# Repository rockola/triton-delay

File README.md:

# triton-delay

Triton Delay v2-3 March 2020 by culturejam/@function_fx

These files v2-3_2 2020-03-27 by rockola

## License

"Triton Delay" by culturejam is licensed under [CC BY-SA 4.0](https://creativecommons.org/licenses/by-sa/4.0/).

## More information

[Triton Delay - Adding the "Glide" from EchoCzar to PT2399](https://www.freestompboxes.org/viewtopic.php?f=13&t=30501) on [freestompboxes.org](https://www.freestompboxes.org/)

## Images

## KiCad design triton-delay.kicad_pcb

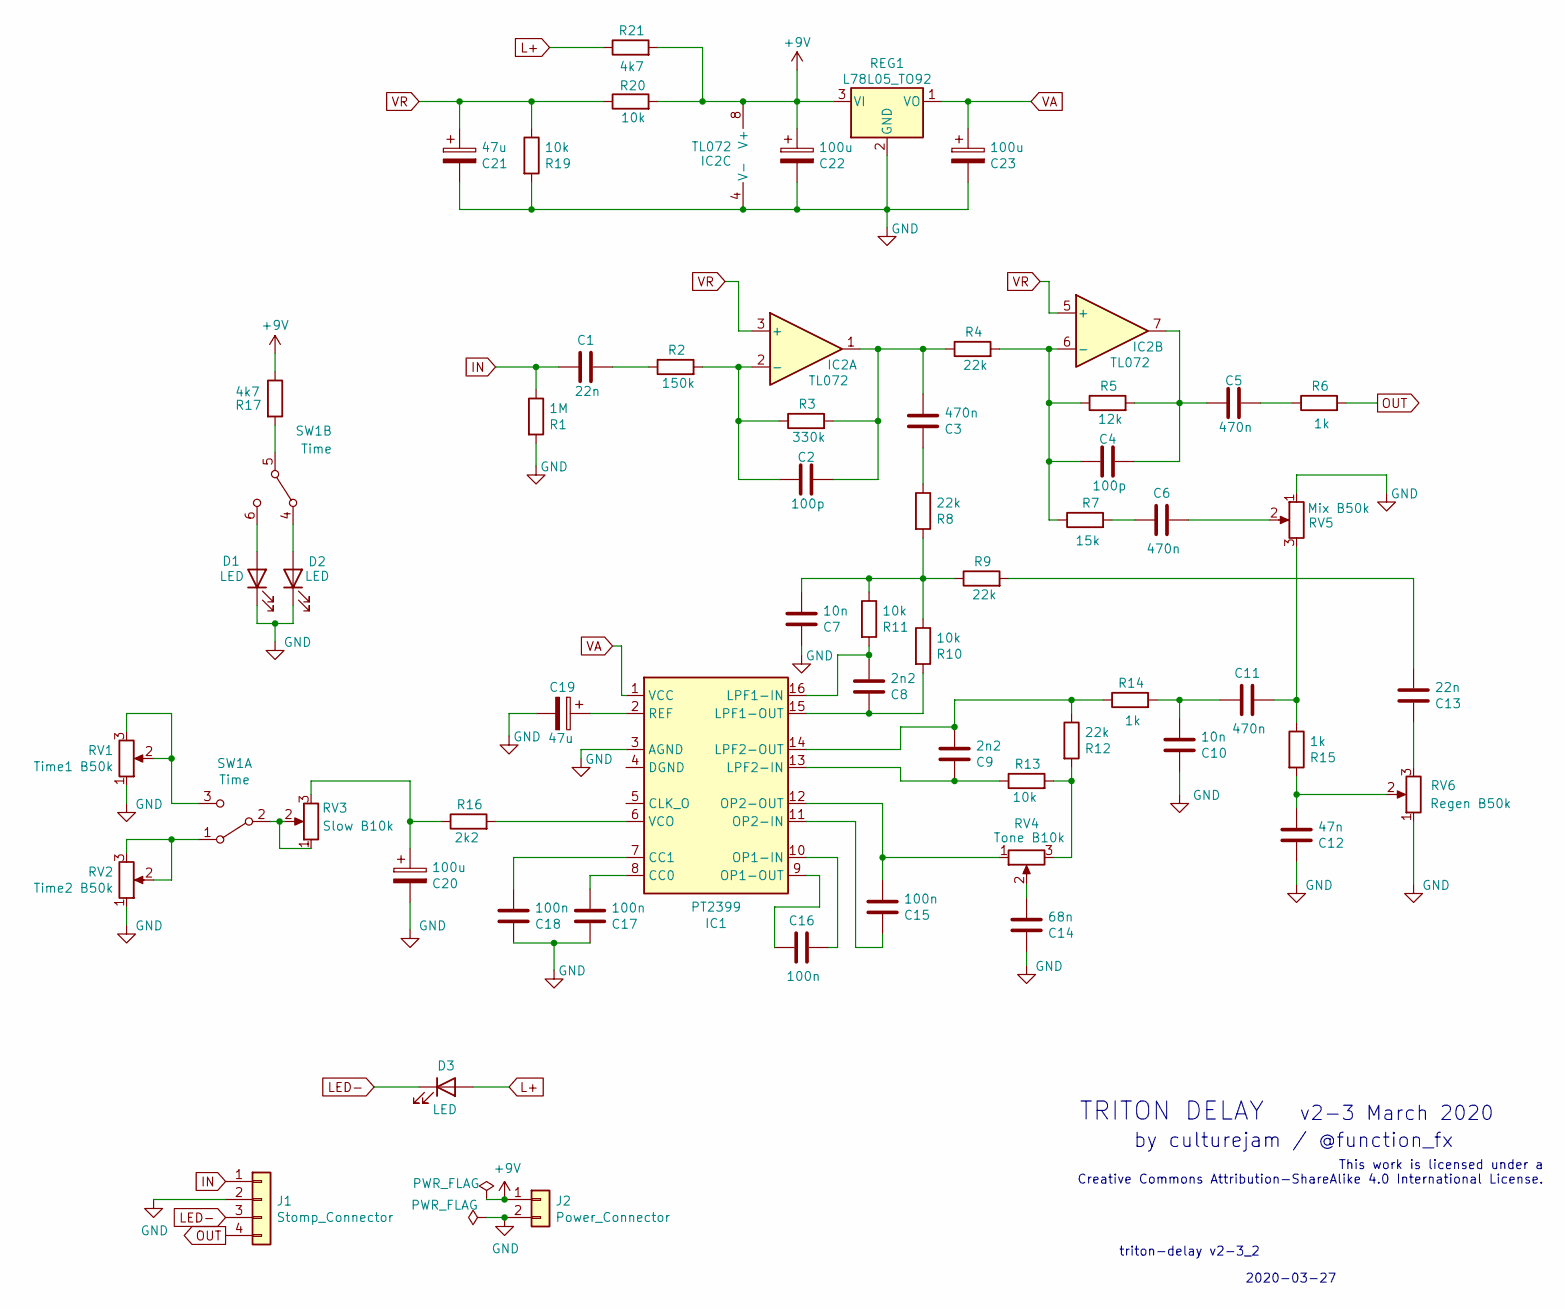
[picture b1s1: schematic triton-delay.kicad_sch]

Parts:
C1, C13: 22n; C_Box_7.2_2.5
C2, C4: 100p; C_Box_7.2_2.5
C3, C5, C6, C11: 470n; C_Box_7.2_4.5
C7, C10: 10n; C_Box_7.2_2.5
C8, C9: 2n2; C_Box_7.2_2.5
C12: 47n; C_Box_7.2_2.5
C14: 68n; C_Box_7.2_2.5
C15, C16, C17, C18: 100n; C_Box_7.2_2.5
C19, C21: 47u; CP_Radial_D6.3mm_P2.50mm
C20, C22, C23: 100u; CP_Radial_D6.3mm_P2.50mm
D1, D2, D3: LED; LED_D3.0mm
IC1: PT2399; DIP-16_W7.62mm_Socket
IC2: TL072; DIP-8_W7.62mm_Socket
J1: Stomp_Connector; Stomp_4pin
J2: Power_Connector; Power_Header_2pin
R1: 1M; R_DIN0207
R2: 150k; R_DIN0207
R3: 330k; R_DIN0207
R4, R8, R9, R12: 22k; R_DIN0207
R5: 12k; R_DIN0207
R6, R14, R15: 1k; R_DIN0207
R7: 15k; R_DIN0207
R10, R11, R13, R19, R20: 10k; R_DIN0207
R16: 2k2; R_DIN0207
R17, R21: 4k7; R_DIN0207
REG1: L78L05_TO92; TO-92_Inline
RV1: Time1 B50k; 16MM_PADS.2
RV2: Time2 B50k; 16MM_PADS.2
RV3: Slow B10k; 16MM_PADS.2
RV4: Tone B10k; 16MM_PADS.2
RV5: Mix B50k; 16MM_PADS.2
RV6: Regen B50k; 16MM_PADS.2
SW1: Time; DPDT.WIRE

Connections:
+9V: C22.1, IC2.8 (V+), J2.1 (PWR), R17.1, R20.2, R21.2, REG1.3 (VI)
GND: C7.2, C10.2, C12.2, C14.2, C17.2, C18.2, C19.2, C20.2, C21.2, C22.2, C23.2, D1.1 (K), D2.1 (K), IC1.3 (AGND), IC2.4 (V-), J1.2 (GND), J2.2 (GND), R1.2, R19.2, REG1.2 (GND), RV1.1, RV2.1, RV5.1, RV6.1
IN: C1.1, J1.1 (IN), R1.1
L+: D3.2 (A), R21.1
LED-: D3.1 (K), J1.3 (SW)
unnamed: C1.2, R2.1
unnamed: C2.1, IC2.2 (-), R2.2, R3.1
unnamed: C2.2, C3.1, IC2.1, R3.2, R4.1
unnamed: C3.2, R8.1
unnamed: C4.1, IC2.6 (-), R4.2, R5.1, R7.1
unnamed: C4.2, C5.1, IC2.7, R5.2
unnamed: C5.2, R6.1
unnamed: C6.1, R7.2
unnamed: C6.2, RV5.2
unnamed: C7.1, R8.2, R9.1, R10.1, R11.1
unnamed: C8.1, IC1.16 (LPF1-IN), R11.2
unnamed: C8.2, IC1.15 (LPF1-OUT), R10.2
unnamed: C9.1, IC1.14 (LPF2-OUT), R12.1, R14.1
unnamed: C9.2, IC1.13 (LPF2-IN), R13.1
unnamed: C10.1, C11.1, R14.2
unnamed: C11.2, R15.1, RV5.3
unnamed: C12.1, R15.2, RV6.2
unnamed: C13.1, R9.2
unnamed: C13.2, RV6.3
unnamed: C14.1, RV4.2
unnamed: C15.1, IC1.12 (OP2-OUT), RV4.1
unnamed: C15.2, IC1.11 (OP2-IN)
unnamed: C16.1, IC1.9 (OP1-OUT)
unnamed: C16.2, IC1.10 (OP1-IN)
unnamed: C17.1, IC1.8 (CC0)
unnamed: C18.1, IC1.7 (CC1)
unnamed: C19.1, IC1.2 (REF)
unnamed: C20.1, R16.1, RV3.3
unnamed: D1.2 (A), SW1.6 (C)
unnamed: D2.2 (A), SW1.4 (A)
unnamed: IC1.6 (VCO), R16.2
unnamed: R12.2, R13.2, RV4.3
unnamed: R17.2, SW1.5 (B)
unnamed: RV1.2, RV1.3, SW1.3 (C)
unnamed: RV2.2, RV2.3, SW1.1 (A)
unnamed: RV3.1, RV3.2, SW1.2 (B)
OUT: J1.4 (OUT), R6.2
VA: C23.1, IC1.1 (VCC), REG1.1 (VO)
VR: C21.1, IC2.3 (+), IC2.5 (+), R19.1, R20.1

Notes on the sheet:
2020-03-27
by culturejam / @function_fx
TRITON DELAY
triton-delay v2-3_2
v2-3 March 2020
This work is licensed under a Creative Commons Attribution-ShareAlike 4.0 International License.

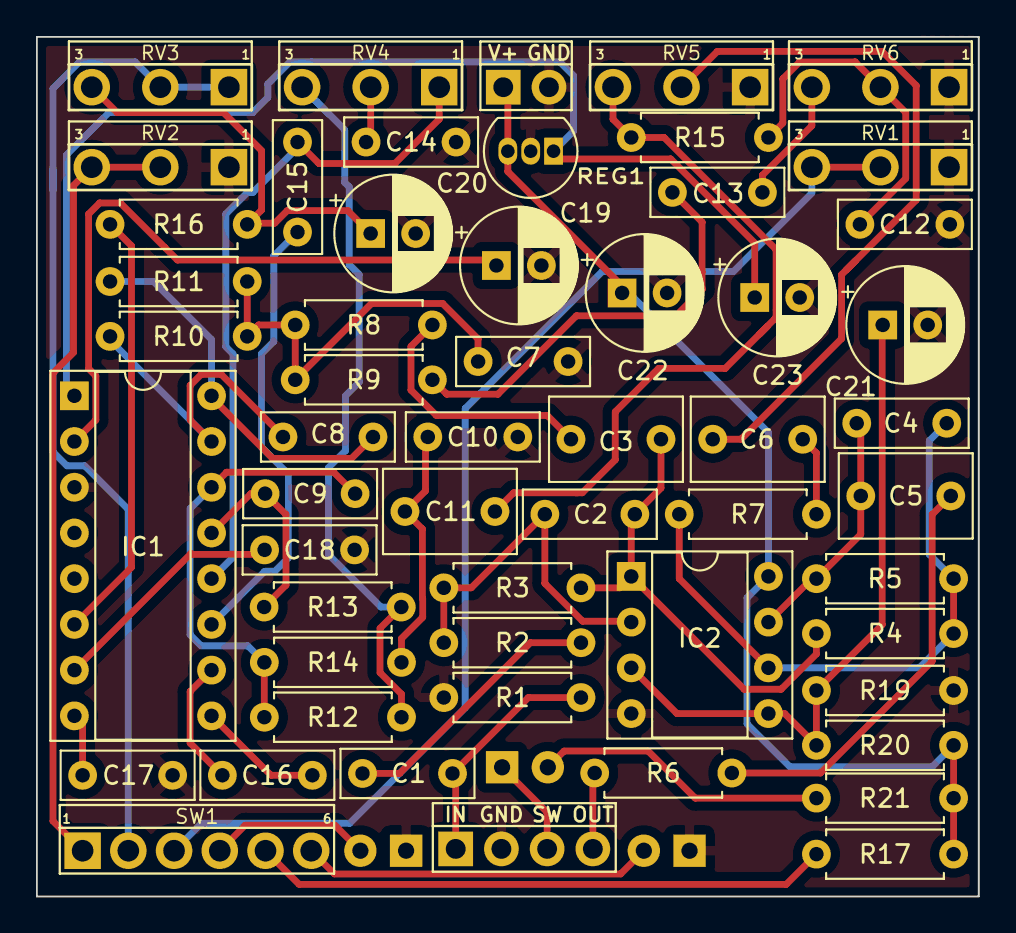
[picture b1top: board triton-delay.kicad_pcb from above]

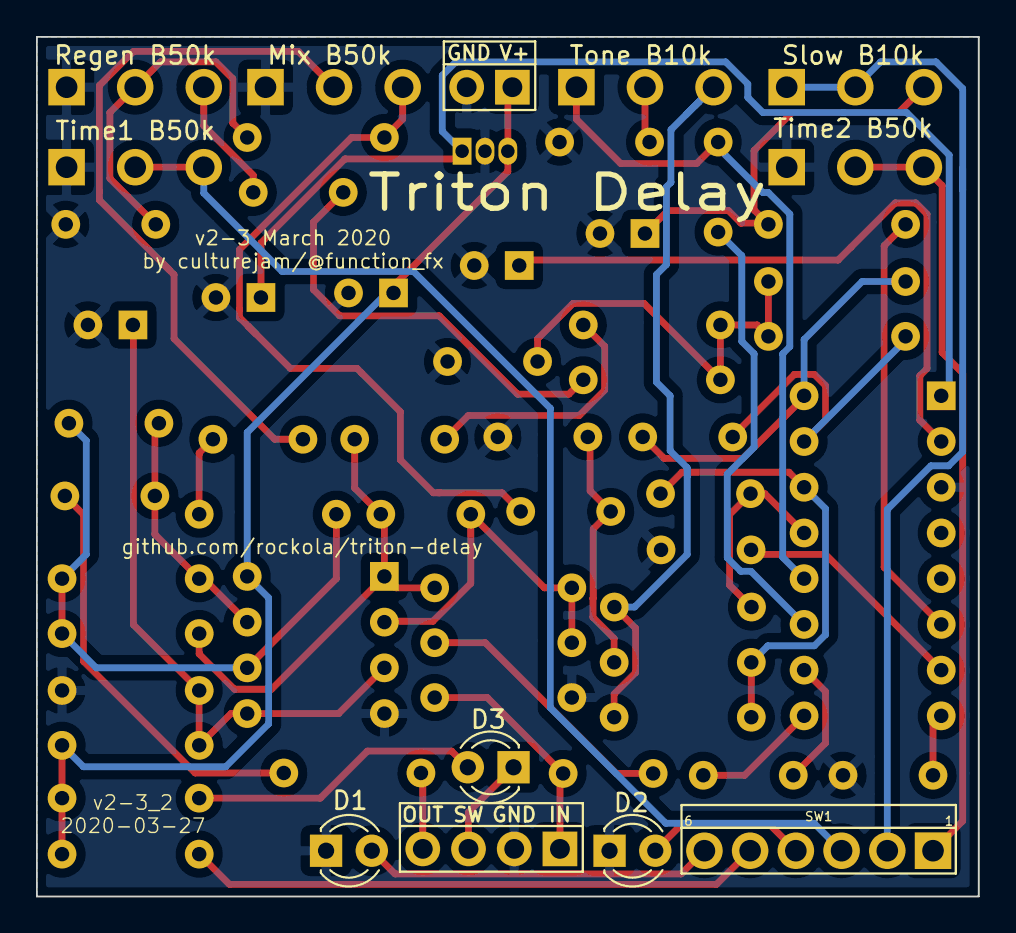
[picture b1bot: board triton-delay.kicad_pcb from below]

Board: 2 copper layers, 52.3 x 47.8 mm, 58 parts (3 on the bottom side), 44 nets.

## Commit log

2020-03-27 v2-3_1: initial version
2020-03-27 pcb images
2020-03-27 markdown fixes
2020-03-27 v2-3_2: tied unused leg 1 of Slow B10k to wiper, moved a few traces for better ground plane coverage
2020-03-27 v2-3_2 pcb images
2022-01-11 ignore backups directory
2022-01-11 updated to KiCad 6.0
